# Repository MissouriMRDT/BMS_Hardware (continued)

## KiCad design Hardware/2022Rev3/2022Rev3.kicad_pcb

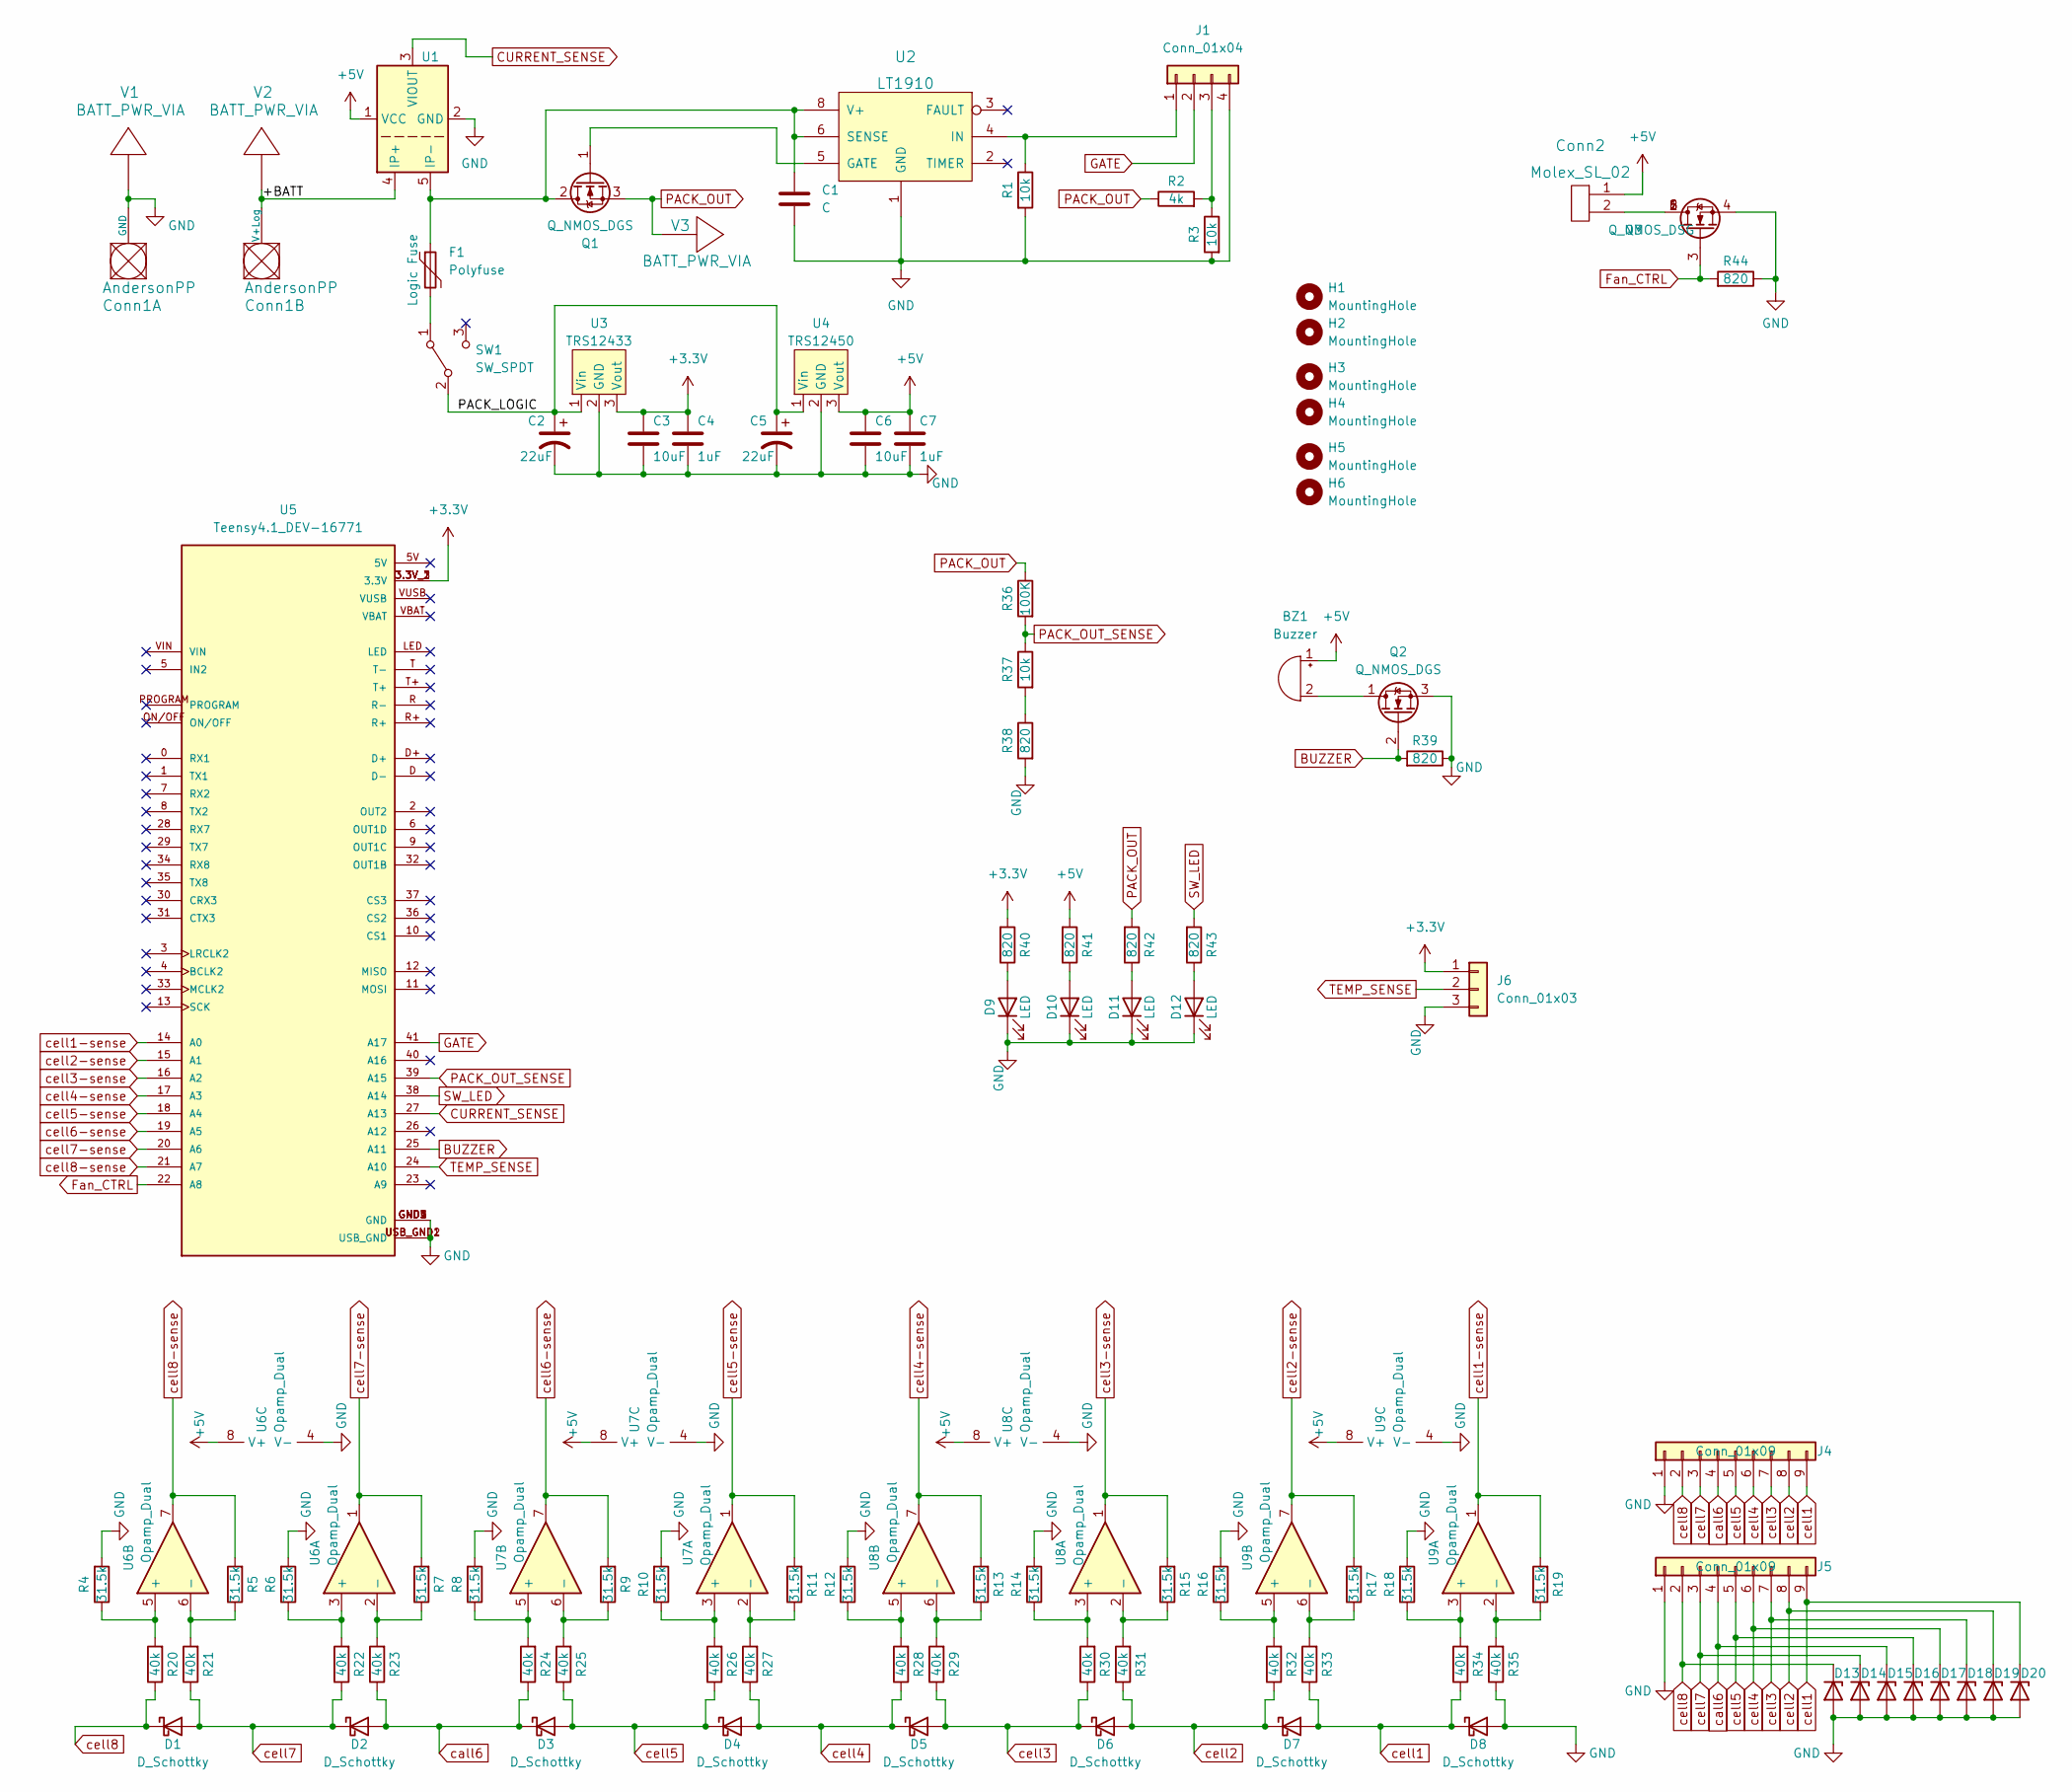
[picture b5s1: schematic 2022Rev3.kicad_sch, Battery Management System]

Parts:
BZ1: Buzzer; BUZZER_SMI_1324_TW_5V_2_R
C1: C; C_0603_1608Metric_Pad1.08x0.95mm_HandSolder
C2, C5: 22uF; CP_Radial_D5.0mm_P2.50mm
C3, C6: 10uF; C_0603_1608Metric_Pad1.08x0.95mm_HandSolder
C4, C7: 1uF; C_0603_1608Metric_Pad1.08x0.95mm_HandSolder
Conn1: AndersonPP; Square_Anderson_2_V_Side_By_Side_PV
Conn2: Molex_SL_02; MOLEX_SL_02_Vertical
D1, D2, D3, D4, D5, D6, D7, D8: D_Schottky; D_0603_1608Metric_Pad1.05x0.95mm_HandSolder
D9, D10, D11, D12: LED; LED_0603_1608Metric_Pad1.05x0.95mm_HandSolder
D13, D14, D15, D16, D17, D18, D19, D20: D_Zener; D_0603_1608Metric_Pad1.05x0.95mm_HandSolder
F1: Polyfuse; Fuse_2920_7451Metric_Pad2.10x5.45mm_HandSolder
H1, H2, H3, H4: MountingHole; 4_40_Hole_Corner
H5, H6: MountingHole; 4_40_Hole
J1: Conn_01x04; MOLEX_SL_04_Vertical
J4, J5: Conn_01x09; MOLEX_SL_09_Vertical
J6: Conn_01x03; MOLEX_SL_03_Vertical
Q1: Q_NMOS_DGS; IRLS3034_TO-263-7_P
Q2: Q_NMOS_DGS; SOT-23_Handsoldering
Q3: Q_NMOS_DSG; SuperSOT-6
R1, R3, R37: 10k; R_0603_1608Metric_Pad0.98x0.95mm_HandSolder
R2: 4k; R_0603_1608Metric_Pad0.98x0.95mm_HandSolder
R4, R5, R6, R7, R8, R9, R10, R11, R12, R13, R14, R15, R16, R17, R18, R19: 31.5k; R_0603_1608Metric_Pad0.98x0.95mm_HandSolder
R20, R21, R22, R23, R24, R25, R26, R27, R28, R29, R30, R31, R32, R33, R34, R35: 40k; R_0603_1608Metric_Pad0.98x0.95mm_HandSolder
R36: 100K; R_0603_1608Metric_Pad0.98x0.95mm_HandSolder
R38, R39, R40, R41, R42, R43, R44: 820; R_0603_1608Metric_Pad0.98x0.95mm_HandSolder
SW1: SW_SPDT; MOLEX_SL_03_Vertical
U1: ACS758xCB-200B-PFF; Allegro_CB_PFF
U2: LT1910; SO-8_3.9x4.9mm_P1.27mm
U3: TRS12433; TSR_1-2433
U4: TRS12450; TSR_1-2433
U5: Teensy4.1_DEV-16771; MODULE_DEV-16771; PARTREV 4.1
U6, U7, U8, U9: Opamp_Dual; SO-8_3.9x4.9mm_P1.27mm
V1, V2, V3: BATT_PWR_VIA

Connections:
+3V3: C3.1, C4.1, J6.1, R40.2, U3.3 (Vout), U5.3.3V_1 (3.3V), U5.3.3V_2 (3.3V), U5.3.3V_3 (3.3V)
+5V: BZ1.1 (-), C6.1, C7.1, Conn2.1, R41.2, U1.1 (VCC), U4.3 (Vout), U6.8 (V+), U7.8 (V+), U8.8 (V+), U9.8 (V+)
/+BATT: Conn1.2 (V+Log), U1.4 (IP+), V2.1
/PACK_LOGIC: C2.1, C5.1, SW1.2 (B), U3.1 (Vin), U4.1 (Vin)
BUZZER: Q2.2 (G), R39.2, U5.25 (A11)
CURRENT_SENSE: U1.3 (VIOUT), U5.27 (A13)
Fan_CTRL: Q3.3 (G), R44.2, U5.22 (A8)
GATE: J1.2, U5.41 (A17)
GND: C1.2, C2.2, C3.2, C4.2, C5.2, C6.2, C7.2, Conn1.1 (GND), D8.2 (A), D9.1 (K), D10.1 (K), D11.1 (K), D12.1 (K), D13.2 (A), D14.2 (A), D15.2 (A), D16.2 (A), D17.2 (A), D18.2 (A), D19.2 (A), D20.2 (A), J1.4, J4.1, J5.1, J6.3, Q2.3 (S), Q3.4 (S), R1.2, R3.2, R4.2, R6.2, R8.2, R10.2, R12.2, R14.2, R16.2, R18.2, R35.1, R38.2, R39.1, R44.1, U1.2 (GND), U2.1 (GND), U3.2 (GND), U4.2 (GND), U5.GND1 (GND), U5.GND2 (GND), U5.GND3 (GND), U5.GND4 (GND), U5.GND5 (GND), U5.USB_GND1 (USB_GND), U5.USB_GND2 (USB_GND), U6.4 (V-), U7.4 (V-), U8.4 (V-), U9.4 (V-), V1.1
unnamed: BZ1.2 (+), Q2.1 (D)
unnamed: C1.1, F1.1, Q1.2 (D), U1.5 (IP-), U2.6 (SENSE), U2.8 (V+)
unnamed: D9.2 (A), R40.1
unnamed: D10.2 (A), R41.1
unnamed: D11.2 (A), R42.1
unnamed: D12.2 (A), R43.1
unnamed: F1.2, SW1.1 (A)
unnamed: J1.1, R1.1, U2.4 (IN)
unnamed: J1.3, R2.2, R3.1
unnamed: Q1.1 (G), U2.5 (GATE)
unnamed: Conn2.2, Q3.1 (D), Q3.2 (D), Q3.5 (D), Q3.6 (D)
unnamed: R10.1, R26.2, U7.3 (+)
unnamed: R11.1, R27.2, U7.2 (-)
unnamed: R12.1, R28.2, U8.5 (+)
unnamed: R13.1, R29.2, U8.6 (-)
unnamed: R14.1, R30.2, U8.3 (+)
unnamed: R15.1, R31.2, U8.2 (-)
unnamed: R16.1, R32.2, U9.5 (+)
unnamed: R17.1, R33.2, U9.6 (-)
unnamed: R18.1, R34.2, U9.3 (+)
unnamed: R19.1, R35.2, U9.2 (-)
unnamed: R4.1, R20.2, U6.5 (+)
unnamed: R5.1, R21.2, U6.6 (-)
unnamed: R6.1, R22.2, U6.3 (+)
unnamed: R7.1, R23.2, U6.2 (-)
unnamed: R8.1, R24.2, U7.5 (+)
unnamed: R9.1, R25.2, U7.6 (-)
unnamed: R37.2, R38.1
PACK_OUT: Q1.3 (S), R2.1, R36.1, R42.2, V3.1
PACK_OUT_SENSE: R36.2, R37.1, U5.39 (A15)
SW_LED: R43.2, U5.38 (A14)
TEMP_SENSE: J6.2, U5.24 (A10)
call6: D2.2 (A), D3.1 (K), D15.1 (K), J4.4, J5.4, R23.1, R24.1
cell1: D7.2 (A), D8.1 (K), D20.1 (K), J4.9, J5.9, R33.1, R34.1
cell1-sense: R19.2, U5.14 (A0), U9.1
cell2: D6.2 (A), D7.1 (K), D19.1 (K), J4.8, J5.8, R31.1, R32.1
cell2-sense: R17.2, U5.15 (A1), U9.7
cell3: D5.2 (A), D6.1 (K), D18.1 (K), J4.7, J5.7, R29.1, R30.1
cell3-sense: R15.2, U5.16 (A2), U8.1
cell4: D4.2 (A), D5.1 (K), D17.1 (K), J4.6, J5.6, R27.1, R28.1
cell4-sense: R13.2, U5.17 (A3), U8.7
cell5: D3.2 (A), D4.1 (K), D16.1 (K), J4.5, J5.5, R25.1, R26.1
cell5-sense: R11.2, U5.18 (A4), U7.1
cell6-sense: R9.2, U5.19 (A5), U7.7
cell7: D1.2 (A), D2.1 (K), D14.1 (K), J4.3, J5.3, R21.1, R22.1
cell7-sense: R7.2, U5.20 (A6), U6.1
cell8: D1.1 (K), D13.1 (K), J4.2, J5.2, R20.1
cell8-sense: R5.2, U5.21 (A7), U6.7

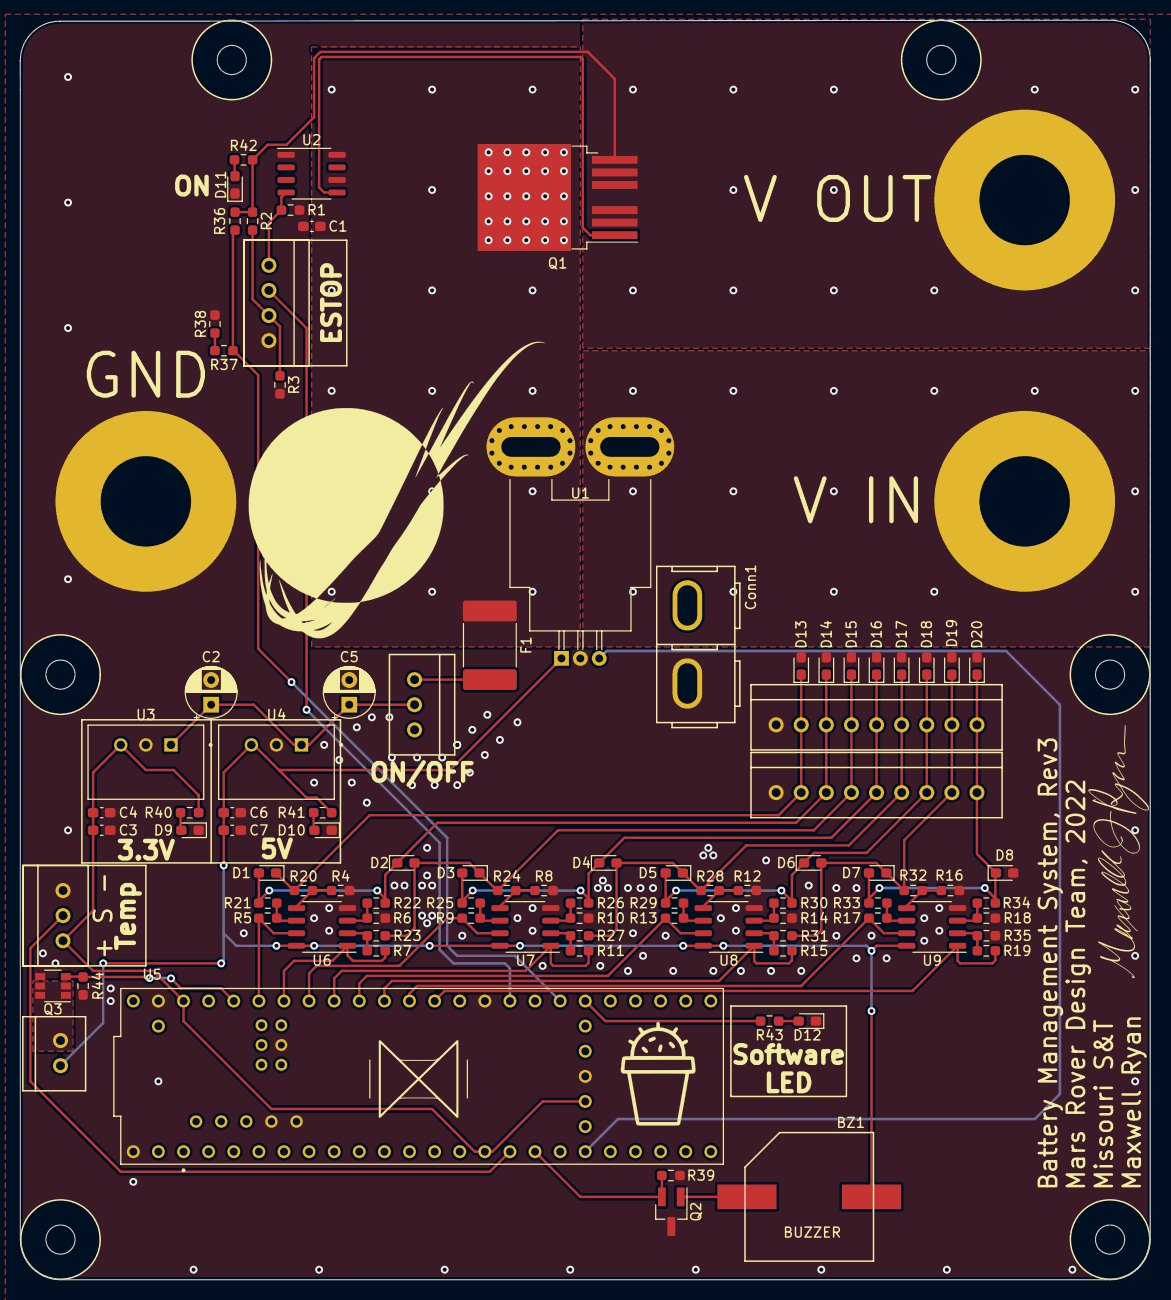
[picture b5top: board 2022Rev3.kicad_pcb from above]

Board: 2 copper layers, 114.3 x 127.4 mm, 101 parts (0 on the bottom side), 57 nets.

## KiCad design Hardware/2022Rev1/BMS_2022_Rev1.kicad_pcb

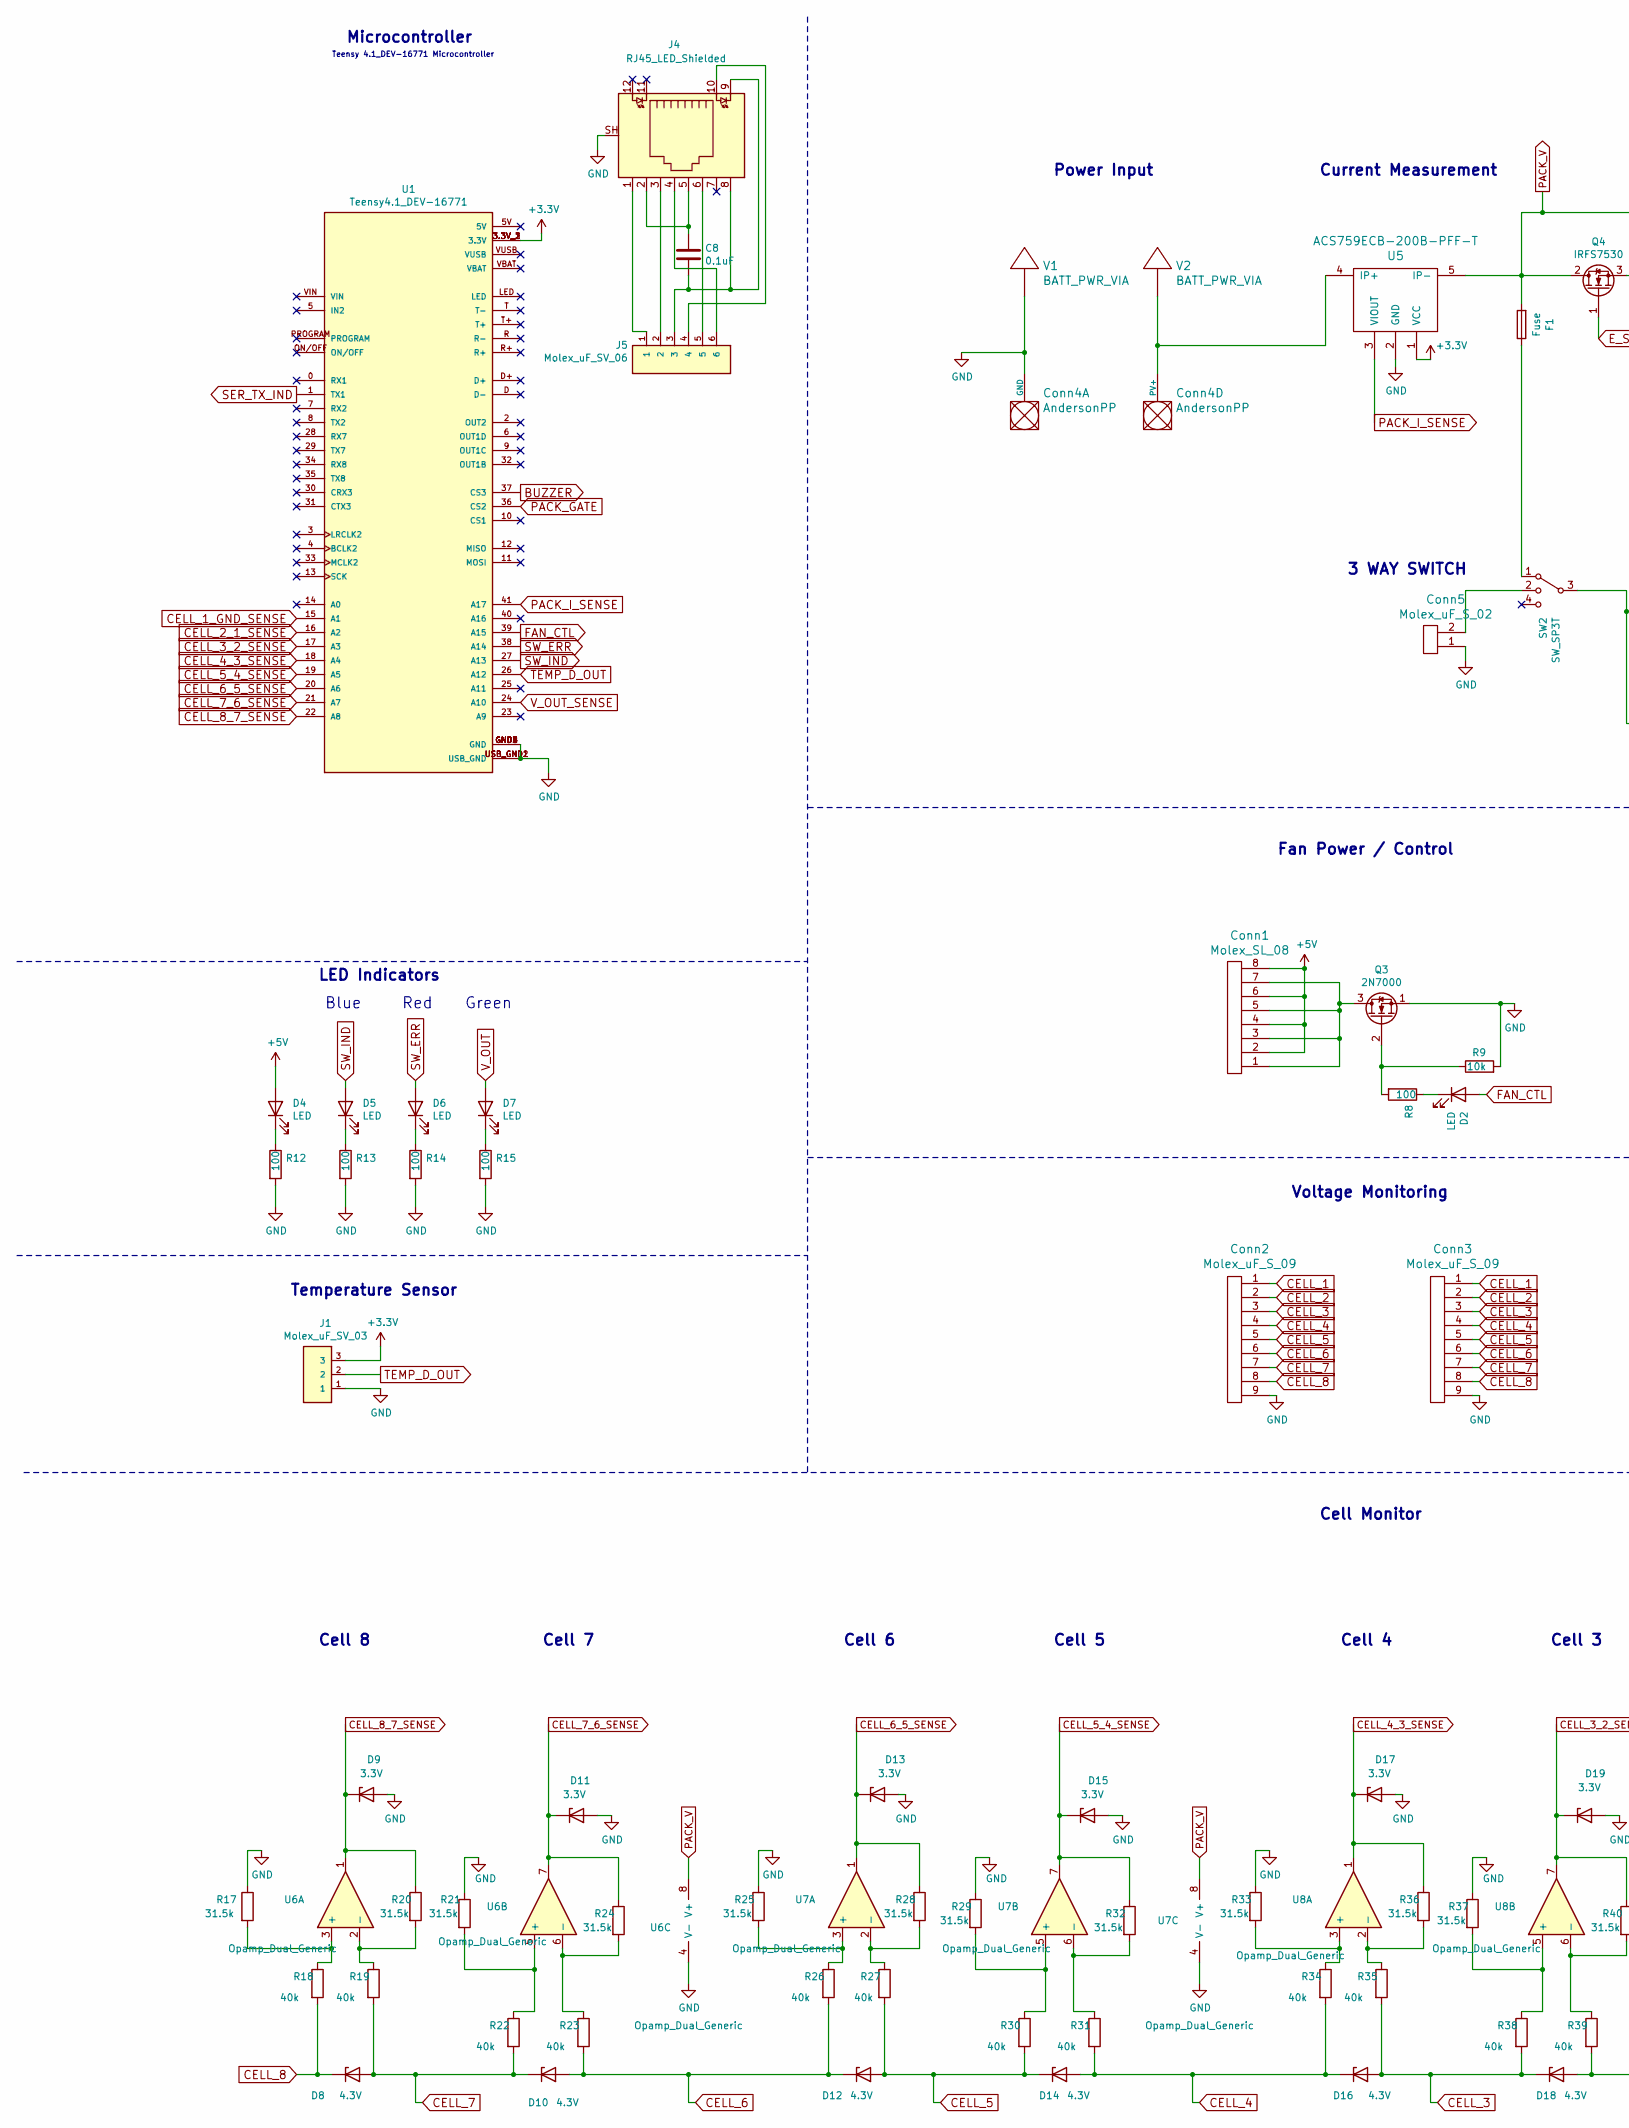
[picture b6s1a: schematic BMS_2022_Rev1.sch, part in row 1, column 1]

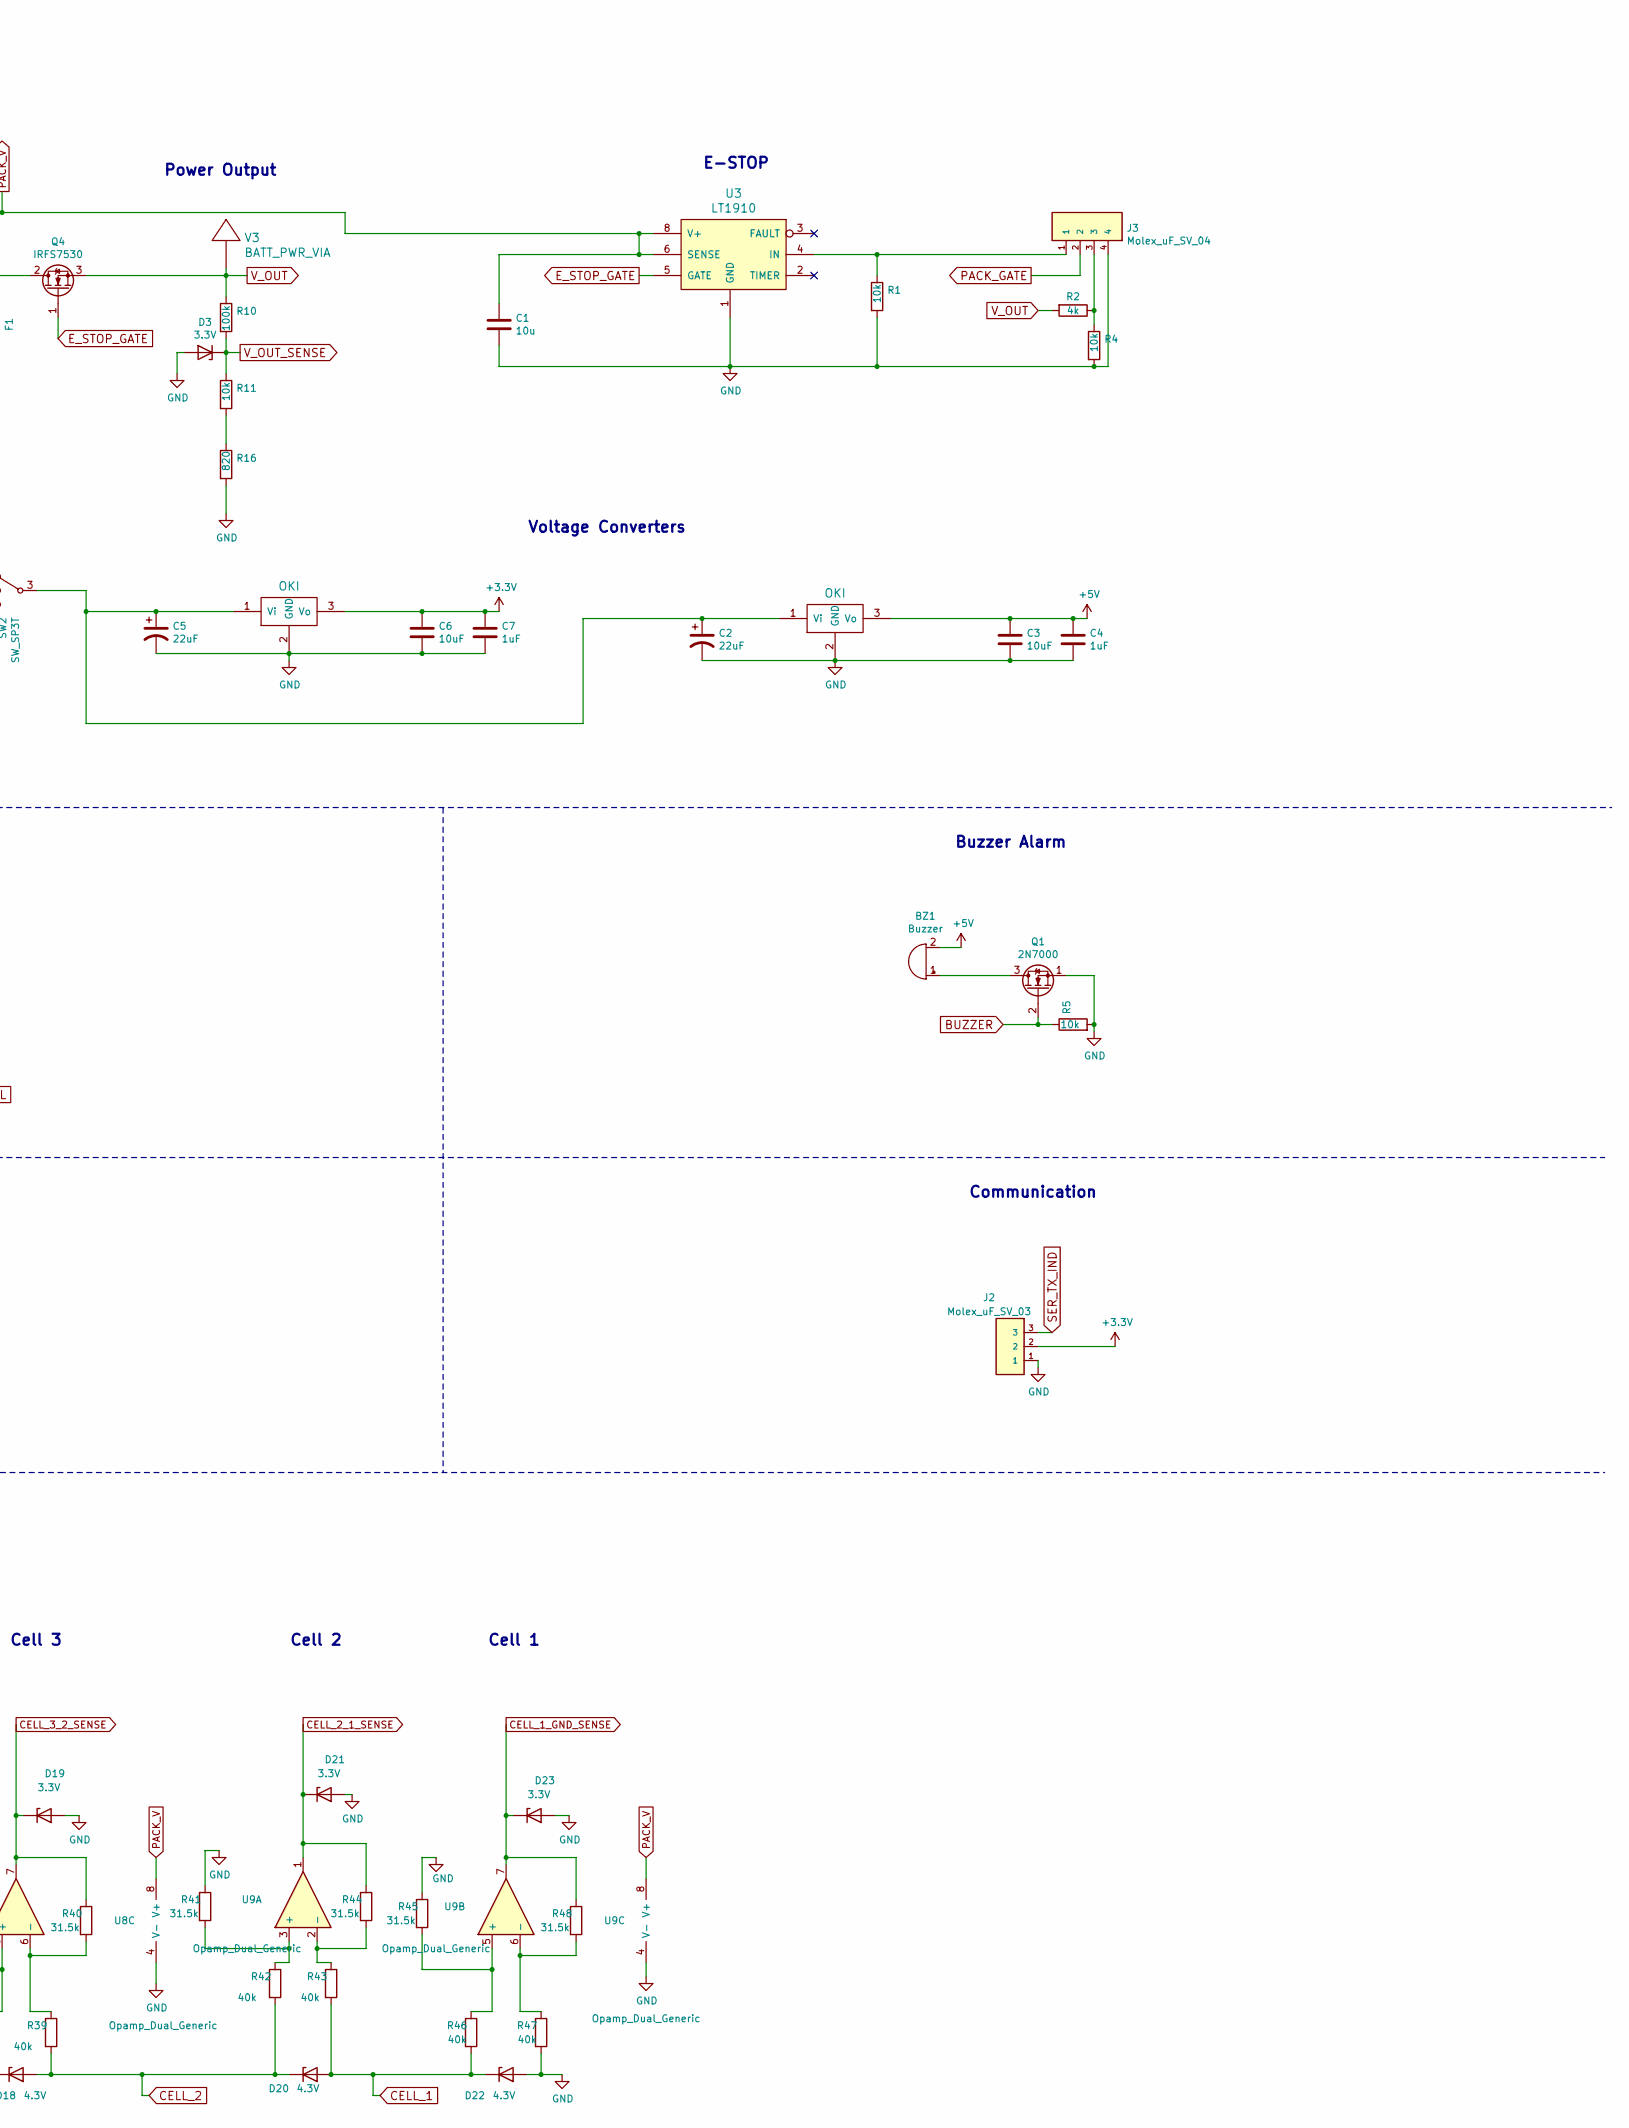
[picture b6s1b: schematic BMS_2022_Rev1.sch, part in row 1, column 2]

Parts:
BZ1: Buzzer; BUZZER_SMI_1324_TW_5V_2_R
C1: 10u; C_0603_1608Metric_Pad1.08x0.95mm_HandSolder
C2, C5: 22uF; CP_Radial_D5.0mm_P2.00mm
C3, C6: 10uF; C_0603_1608Metric_Pad1.08x0.95mm_HandSolder
C4, C7: 1uF; C_0603_1608Metric_Pad1.08x0.95mm_HandSolder
C8: 0.1uF; C_0603_1608Metric_Pad1.08x0.95mm_HandSolder
Conn1: Molex_SL_08; MOLEX_uF_S_08_Vertical
Conn2, Conn3: Molex_uF_S_09; MOLEX_uF_S_09_Vertical
Conn4: AndersonPP; Anderson_2_Vertical_Side_by_Side_PV
Conn5: Molex_uF_S_02; MOLEX_uF_S_02_Vertical
D2: LED; LED_0603_1608Metric_Pad1.05x0.95mm_HandSolder
D3, D9, D11, D13, D15, D17, D19, D21, D23: 3.3V; D_SOT-23_ANK
D4, D5, D6, D7: LED; D_0603_1608Metric_Pad1.05x0.95mm_HandSolder
D8, D10, D12, D14, D16, D18, D20, D22: 4.3V; D_SOT-23_ANK
F1: Fuse; Fuse_2920_7451Metric
J1, J2: Molex_uF_SV_03; MOLEX_uF_S_03_Vertical
J3: Molex_uF_SV_04; MOLEX_uF_S_04_Vertical
J4: RJ45_LED_Shielded; RJ45_Teensy
J5: Molex_uF_SV_06; PinSocket_2x03_P2.00mm_Vertical
Q1, Q3: 2N7000; TO-92_Inline
Q4: IRFS7530; IRLS3034_TO-263-7_P
R1, R4, R5, R9, R11: 10k; R_0603_1608Metric_Pad0.98x0.95mm_HandSolder
R2: 4k; R_0603_1608Metric_Pad0.98x0.95mm_HandSolder
R8, R12, R13, R14, R15: 100; R_0603_1608Metric_Pad0.98x0.95mm_HandSolder
R10: 100k; R_0603_1608Metric_Pad0.98x0.95mm_HandSolder
R16: 820; R_0603_1608Metric_Pad0.98x0.95mm_HandSolder
R17, R20, R21, R24, R25, R28, R29, R32, R33, R36, R37, R40, R41, R44, R45, R48: 31.5k; R_0603_1608Metric_Pad0.98x0.95mm_HandSolder
R18, R19, R22, R23, R26, R27, R30, R31, R34, R35, R38, R39, R42, R43, R46, R47: 40k; R_0603_1608Metric_Pad0.98x0.95mm_HandSolder
SW2: SW_SP3T; MOLEX_uF_S_03_Vertical
U1: Teensy4.1_DEV-16771; MODULE_DEV-16771; PARTREV 4.1
U2, U4: OKI; OKI_Horizontal
U3: LT1910; SOIC-8_5.275x5.275mm_P1.27mm
U5: ACS759ECB-200B-PFF-T; ACS759ECB_PFF_Leadform_5pins
U6, U7, U8, U9: Opamp_Dual_Generic; SOIC-8_5.275x5.275mm_P1.27mm
V1, V2, V3: BATT_PWR_VIA

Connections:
+3V3: C6.1, C7.1, J1.3, J2.2, U1.3.3V_1 (3.3V), U1.3.3V_2 (3.3V), U1.3.3V_3 (3.3V), U2.3 (Vo), U5.1 (VCC)
+5V: BZ1.2 (+), C3.1, C4.1, Conn1.2, Conn1.4, Conn1.6, Conn1.8, D4.2 (A), U4.3 (Vo)
BUZZER: Q1.2 (G), R5.1, U1.37 (CS3)
CELL_1: Conn2.1, Conn3.1, D20.2 (A), D22.1 (K), R43.2, R46.2
CELL_1_GND_SENSE: D23.1 (K), R48.1, U1.15 (A1), U9.7
CELL_2: Conn2.2, Conn3.2, D18.2 (A), D20.1 (K), R39.2, R42.2
CELL_2_1_SENSE: D21.1 (K), R44.1, U1.16 (A2), U9.1
CELL_3: Conn2.3, Conn3.3, D16.2 (A), D18.1 (K), R35.2, R38.2
CELL_3_2_SENSE: D19.1 (K), R40.1, U1.17 (A3), U8.7
CELL_4: Conn2.4, Conn3.4, D14.2 (A), D16.1 (K), R31.2, R34.2
CELL_4_3_SENSE: D17.1 (K), R36.1, U1.18 (A4), U8.1
CELL_5: Conn2.5, Conn3.5, D12.2 (A), D14.1 (K), R27.2, R30.2
CELL_5_4_SENSE: D15.1 (K), R32.1, U1.19 (A5), U7.7
CELL_6: Conn2.6, Conn3.6, D10.2 (A), D12.1 (K), R23.2, R26.2
CELL_6_5_SENSE: D13.1 (K), R28.1, U1.20 (A6), U7.1
CELL_7: Conn2.7, Conn3.7, D8.2 (A), D10.1 (K), R19.2, R22.2
CELL_7_6_SENSE: D11.1 (K), R24.1, U1.21 (A7), U6.7
CELL_8: Conn2.8, Conn3.8, D8.1 (K), R18.2
CELL_8_7_SENSE: D9.1 (K), R20.1, U1.22 (A8), U6.1
E_STOP_GATE: Q4.1 (G), U3.5 (GATE)
FAN_CTL: D2.2 (A), U1.39 (A15)
GND: C1.2, C2.2, C3.2, C4.2, C5.2, C6.2, C7.2, Conn2.9, Conn3.9, Conn4.1 (GND), Conn5.1, D3.2 (A), D9.2 (A), D11.2 (A), D13.2 (A), D15.2 (A), D17.2 (A), D19.2 (A), D21.2 (A), D22.2 (A), D23.2 (A), J1.1, J2.1, J3.4, J4.SH, Q1.1 (S), Q3.1 (S), R1.2, R4.2, R5.2, R9.2, R12.2, R13.2, R14.2, R15.2, R16.2, R17.1, R21.1, R25.1, R29.1, R33.1, R37.1, R41.1, R45.1, R47.2, U1.GND1 (GND), U1.GND2 (GND), U1.GND3 (GND), U1.GND4 (GND), U1.GND5 (GND), U1.USB_GND1 (USB_GND), U1.USB_GND2 (USB_GND), U2.2 (GND), U3.1 (GND), U4.2 (GND), U5.2 (GND), U6.4 (V-), U7.4 (V-), U8.4 (V-), U9.4 (V-), V1.1
unnamed: BZ1.1 (-), Q1.3 (D)
unnamed: C2.1, C5.1, SW2.3, U2.1 (Vi), U4.1 (Vi)
unnamed: C8.1, J4.2, J4.5
unnamed: C8.2, J4.8, J4.9, J5.3
unnamed: Conn1.1, Conn1.3, Conn1.5, Conn1.7, Q3.3 (D)
unnamed: Conn4.4 (PV+), U5.4 (IP+), V2.1
unnamed: Conn5.2, SW2.2
unnamed: D2.1 (K), R8.1
unnamed: D4.1 (K), R12.1
unnamed: D5.1 (K), R13.1
unnamed: D6.1 (K), R14.1
unnamed: D7.1 (K), R15.1
unnamed: F1.1, SW2.1
unnamed: J3.1, R1.1, U3.4 (IN)
unnamed: J3.3, R2.1, R4.1
unnamed: J4.1, J5.1
unnamed: J4.3, J5.2
unnamed: J4.4, J5.6
unnamed: J4.6, J5.5
unnamed: J4.10, J5.4
unnamed: Q3.2 (G), R8.2, R9.1
unnamed: R11.2, R16.1
unnamed: R17.2, R18.1, U6.3 (+)
unnamed: R19.1, R20.2, U6.2 (-)
unnamed: R21.2, R22.1, U6.5 (+)
unnamed: R23.1, R24.2, U6.6 (-)
unnamed: R25.2, R26.1, U7.3 (+)
unnamed: R27.1, R28.2, U7.2 (-)
unnamed: R29.2, R30.1, U7.5 (+)
unnamed: R31.1, R32.2, U7.6 (-)
unnamed: R33.2, R34.1, U8.3 (+)
unnamed: R35.1, R36.2, U8.2 (-)
unnamed: R37.2, R38.1, U8.5 (+)
unnamed: R39.1, R40.2, U8.6 (-)
unnamed: R41.2, R42.1, U9.3 (+)
unnamed: R43.1, R44.2, U9.2 (-)
unnamed: R45.2, R46.1, U9.5 (+)
unnamed: R47.1, R48.2, U9.6 (-)
PACK_GATE: J3.2, U1.36 (CS2)
PACK_I_SENSE: U1.41 (A17), U5.3 (VIOUT)
PACK_V: C1.1, F1.2, Q4.2 (D), U3.6 (SENSE), U3.8 (V+), U5.5 (IP-), U6.8 (V+), U7.8 (V+), U8.8 (V+), U9.8 (V+)
SER_TX_IND: J2.3, U1.1 (TX1)
SW_ERR: D6.2 (A), U1.38 (A14)
SW_IND: D5.2 (A), U1.27 (A13)
TEMP_D_OUT: J1.2, U1.26 (A12)
V_OUT: D7.2 (A), Q4.3 (S), R2.2, R10.1, V3.1
V_OUT_SENSE: D3.1 (K), R10.2, R11.1, U1.24 (A10)

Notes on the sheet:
Microcontroller
Teensy 4.1_DEV-16771 Microcontroller
E-STOP
Buzzer Alarm
Fan Power / Control
LED Indicators
Communication
Voltage Converters
Blue
Red
Green
Cell Monitor
Power Input
Current Measurement
Temperature Sensor
Voltage Monitoring
3 WAY SWITCH
Power Output
Cell 1
Cell 2
Cell 3
Cell 4
Cell 5
Cell 6
Cell 7
Cell 8

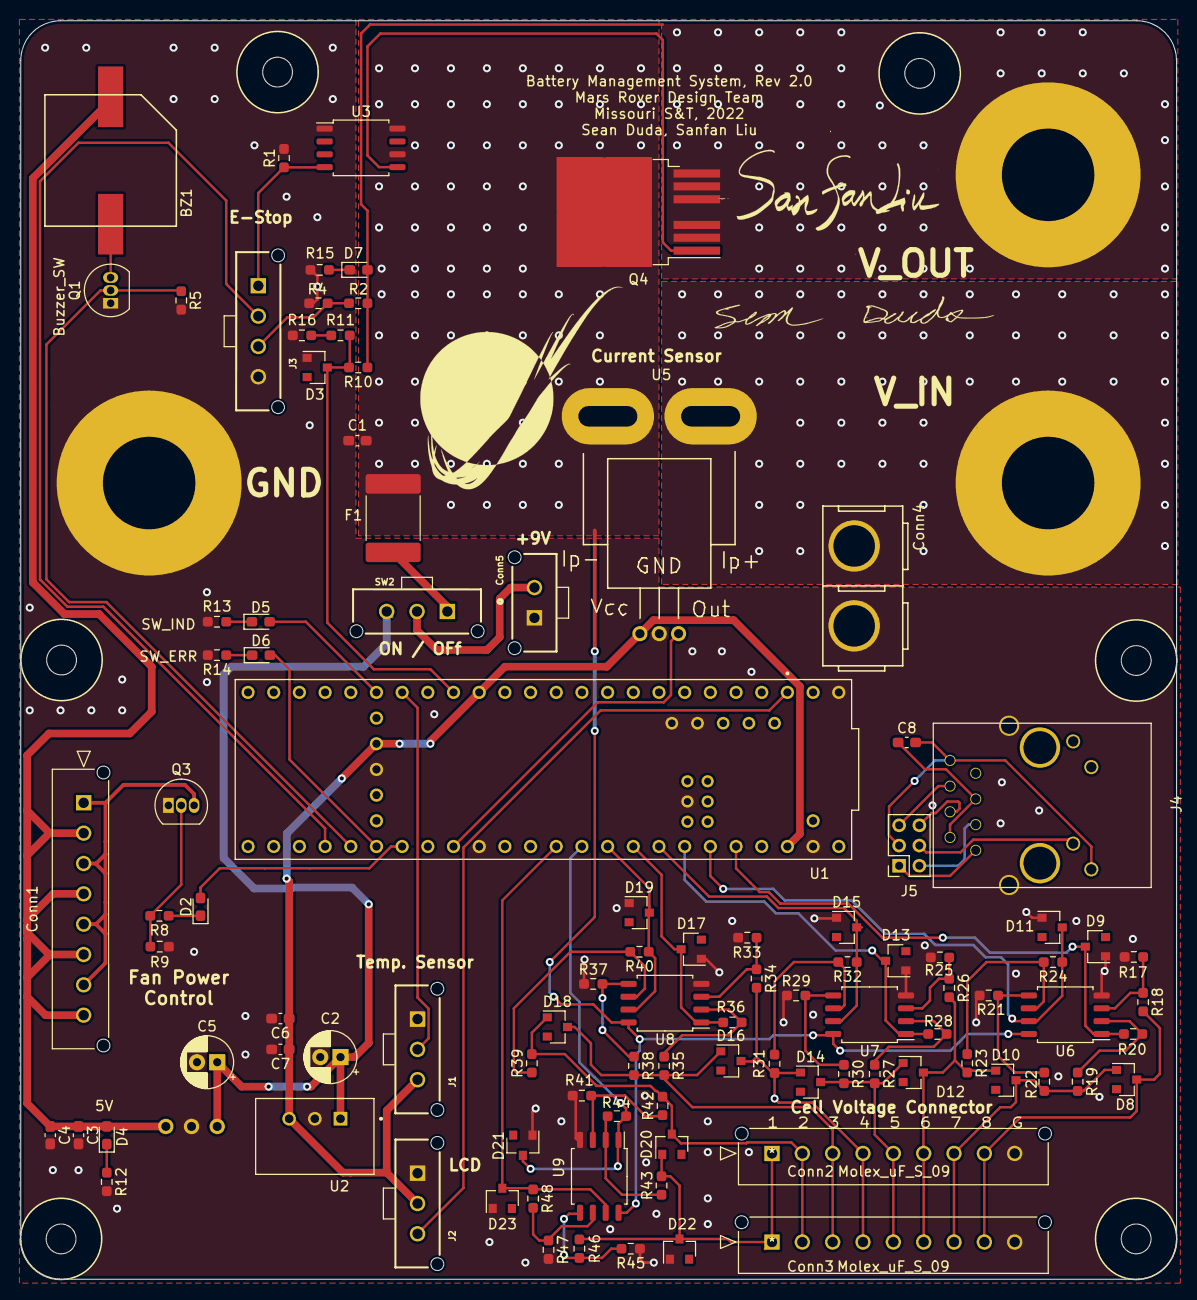
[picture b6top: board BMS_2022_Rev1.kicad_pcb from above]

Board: 2 copper layers, 114.3 x 124.5 mm, 103 parts (1 on the bottom side), 69 nets.
